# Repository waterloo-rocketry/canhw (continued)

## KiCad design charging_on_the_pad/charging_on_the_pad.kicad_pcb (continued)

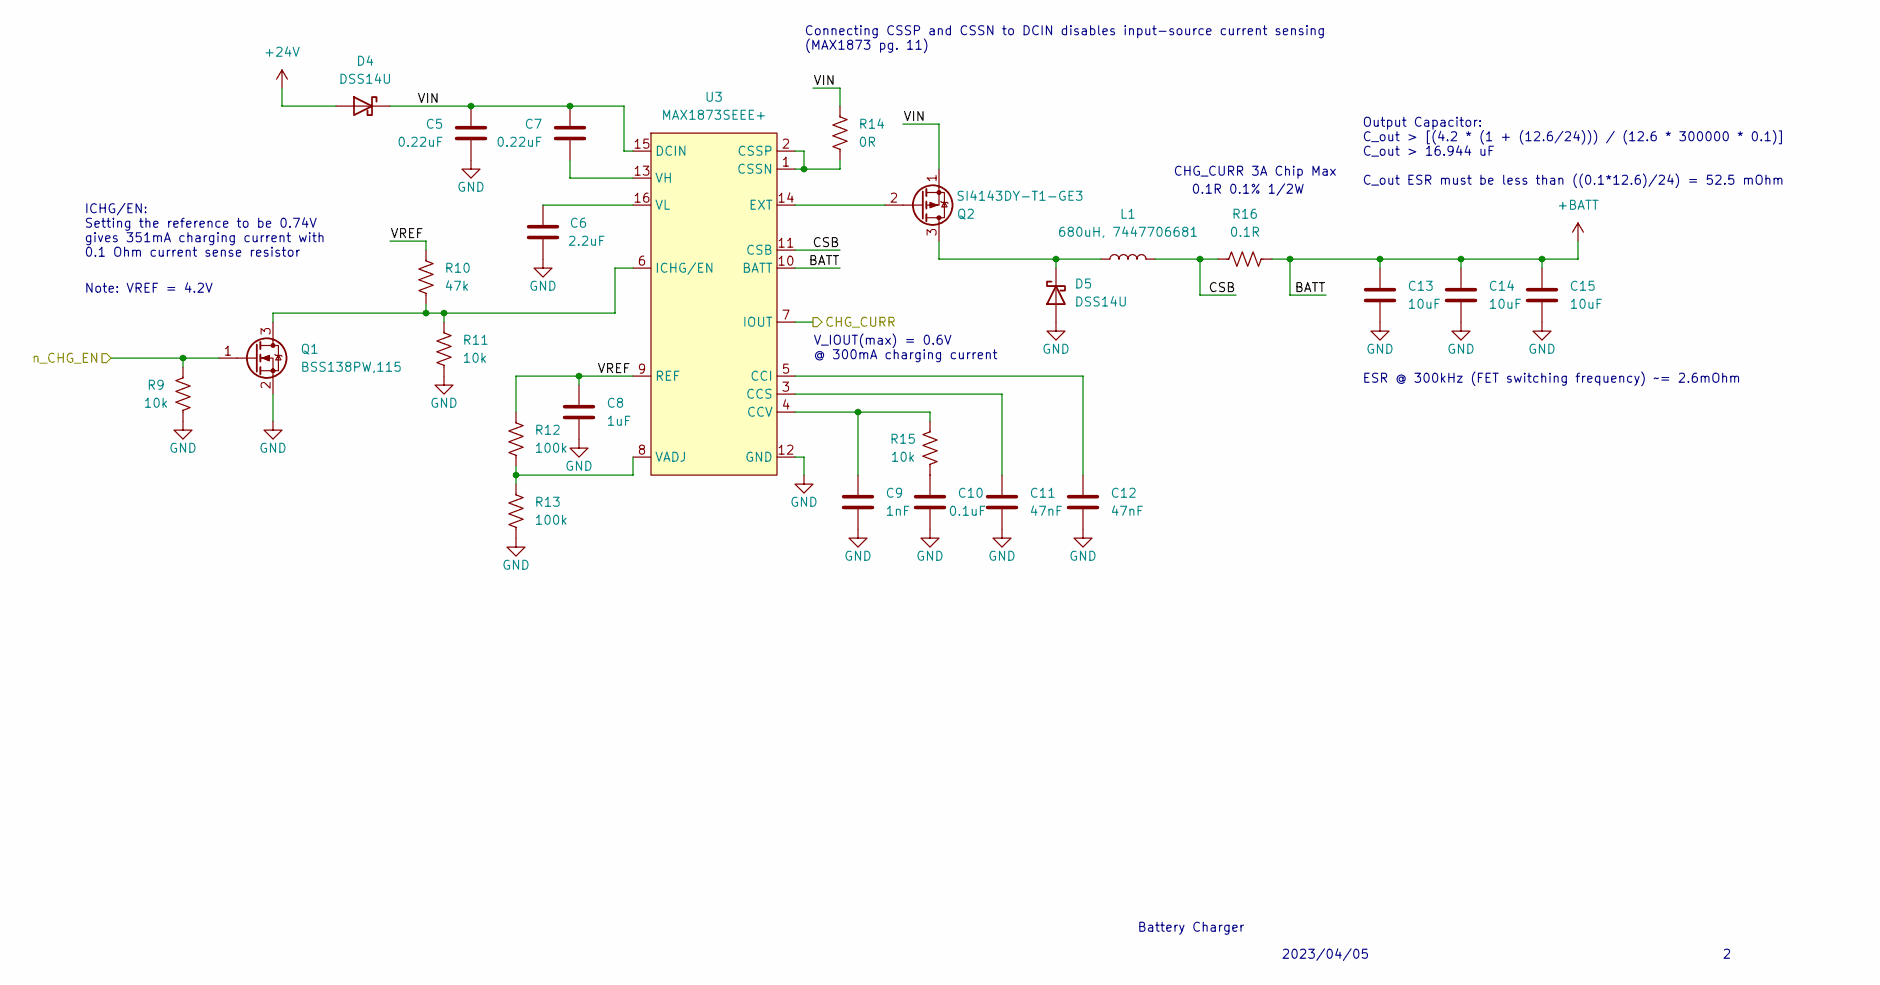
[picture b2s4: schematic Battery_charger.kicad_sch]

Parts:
C5, C7: 0.22uF; C_0805_2012Metric_Pad1.18x1.45mm_HandSolder
C6: 2.2uF; C_0805_2012Metric_Pad1.18x1.45mm_HandSolder
C8: 1uF; C_0805_2012Metric_Pad1.18x1.45mm_HandSolder
C9: 1nF; C_0805_2012Metric_Pad1.18x1.45mm_HandSolder
C10: 0.1uF; C_0805_2012Metric_Pad1.18x1.45mm_HandSolder
C11, C12: 47nF; C_0805_2012Metric_Pad1.18x1.45mm_HandSolder
C13, C14, C15: 10uF; C_0805_2012Metric_Pad1.18x1.45mm_HandSolder
D4, D5: DSS14U
L1: 680uH, 7447706681; L_12x12mm_H6mm
Q1: BSS138PW,115; SOT-323_SC-70_Handsoldering
Q2: SI4143DY-T1-GE3
R9, R11, R15: 10k; R_0805_2012Metric_Pad1.20x1.40mm_HandSolder
R10: 47k; R_0805_2012Metric_Pad1.20x1.40mm_HandSolder
R12, R13: 100k; R_0805_2012Metric_Pad1.20x1.40mm_HandSolder
R14: 0R; R_0805_2012Metric_Pad1.20x1.40mm_HandSolder
R16: 0.1R; R_1206_3216Metric_Pad1.30x1.75mm_HandSolder
U3: MAX1873SEEE+; SSOP-16_3.9x4.9mm_P0.635mm

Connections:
+24V: D4.2 (A); also elsewhere on the board
+BATT: C13.2, C14.2, C15.2, R16.1, U3.10 (BATT); also elsewhere on the board
/Battery Charger/CSB: L1.2, R16.2, U3.11 (CSB)
/Battery Charger/VIN: C5.2, C7.2, D4.1 (K), Q2.1 (S), R14.1, U3.15 (DCIN)
/Battery Charger/VREF: C8.2, R10.1, R12.1, U3.9 (REF)
/CHG_CURR: U3.7 (IOUT); also elsewhere on the board
/n_CHG_EN: Q1.1 (G), R9.2; also elsewhere on the board
GND: C5.1, C6.1, C8.1, C9.2, C10.1, C11.1, C12.1, C13.1, C14.1, C15.1, D5.2 (A), Q1.2 (S), R9.1, R11.2, R13.2, U3.12 (GND); also elsewhere on the board
unnamed: C10.2, R15.1
unnamed: D5.1 (K), L1.1, Q2.3 (D)
unnamed: Q1.3 (D), R10.2, R11.1, U3.6 (ICHG/EN)
unnamed: Q2.2 (G), U3.14 (EXT)
unnamed: C12.2, U3.5 (CCI)
unnamed: C11.2, U3.3 (CCS)
unnamed: C9.1, R15.2, U3.4 (CCV)
unnamed: R14.2, U3.1 (CSSN), U3.2 (CSSP)
unnamed: R12.2, R13.1, U3.8 (VADJ)
unnamed: C7.1, U3.13 (VH)
unnamed: C6.2, U3.16 (VL)

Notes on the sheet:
V_IOUT(max) = 0.6V @ 300mA charging current
Output Capacitor: C_out > [(4.2 * (1 + (12.6/24))) / (12.6 * 300000 * 0.1)] C_out > 16.944 uF C_out ESR must be less than ((0.1*12.6)/24) = 52.5 mOhm
CHG_CURR 3A Chip Max
Battery Charger
0.1R 0.1% 1/2W
2023/04/05
Note: VREF = 4.2V
ESR @ 300kHz (FET switching frequency) ~= 2.6mOhm
ICHG/EN: Setting the reference to be 0.74V gives 351mA charging current with 0.1 Ohm current sense resistor
Connecting CSSP and CSSN to DCIN disables input-source current sensing (MAX1873 pg. 11)

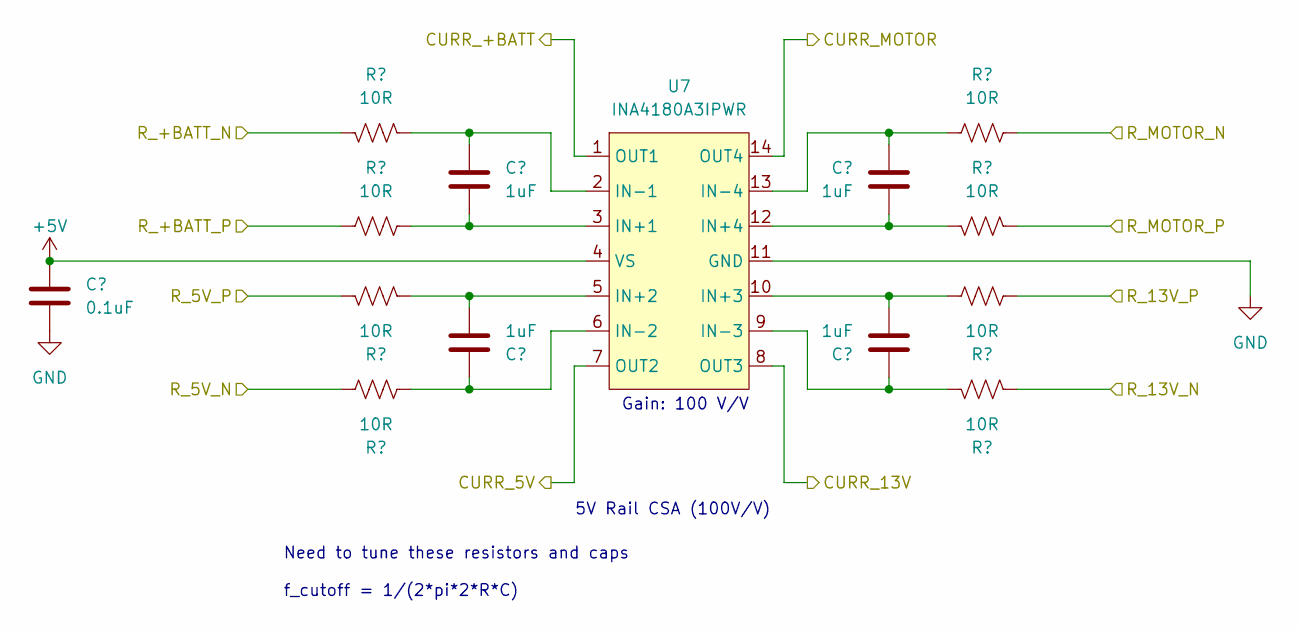
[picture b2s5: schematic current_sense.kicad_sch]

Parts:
C31: 0.1uF; C_0805_2012Metric_Pad1.18x1.45mm_HandSolder
C32, C33, C34, C35: 1uF; C_0805_2012Metric_Pad1.18x1.45mm_HandSolder
R28, R29, R30, R31, R32, R33, R34, R35: 10R; R_0805_2012Metric_Pad1.20x1.40mm_HandSolder
U7: INA4180A3IPWR; TSSOP-14_4.4x5mm_P0.65mm

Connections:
+5V: C31.1, R31.2, U7.4 (VS); also elsewhere on the board
+13V: R35.2; also elsewhere on the board
+BATT: R29.1; also elsewhere on the board
/CURR_5V: U7.7 (OUT2); also elsewhere on the board
/CURR_13V: U7.8 (OUT3); also elsewhere on the board
/CURR_+BATT: U7.1 (OUT1); also elsewhere on the board
/CURR_MOTOR: U7.14 (OUT4); also elsewhere on the board
/Power/R_5V_P: R30.1; also elsewhere on the board
/Power/R_13V_P: R34.1; also elsewhere on the board
/Power/R_+BATT_N: R28.2; also elsewhere on the board
/R_MOTOR_N: R32.2; also elsewhere on the board
/R_MOTOR_P: R33.1; also elsewhere on the board
GND: C31.2, U7.11 (GND); also elsewhere on the board
unnamed: C32.2, R29.2, U7.3 (IN+1)
unnamed: C33.2, R30.2, U7.5 (IN+2)
unnamed: C35.2, R34.2, U7.10 (IN+3)
unnamed: C34.2, R33.2, U7.12 (IN+4)
unnamed: C32.1, R28.1, U7.2 (IN-1)
unnamed: C33.1, R31.1, U7.6 (IN-2)
unnamed: C35.1, R35.1, U7.9 (IN-3)
unnamed: C34.1, R32.1, U7.13 (IN-4)

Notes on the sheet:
Gain: 100 V/V
Need to tune these resistors and caps f_cutoff = 1/(2*pi*2*R*C)
5V Rail CSA (100V/V)

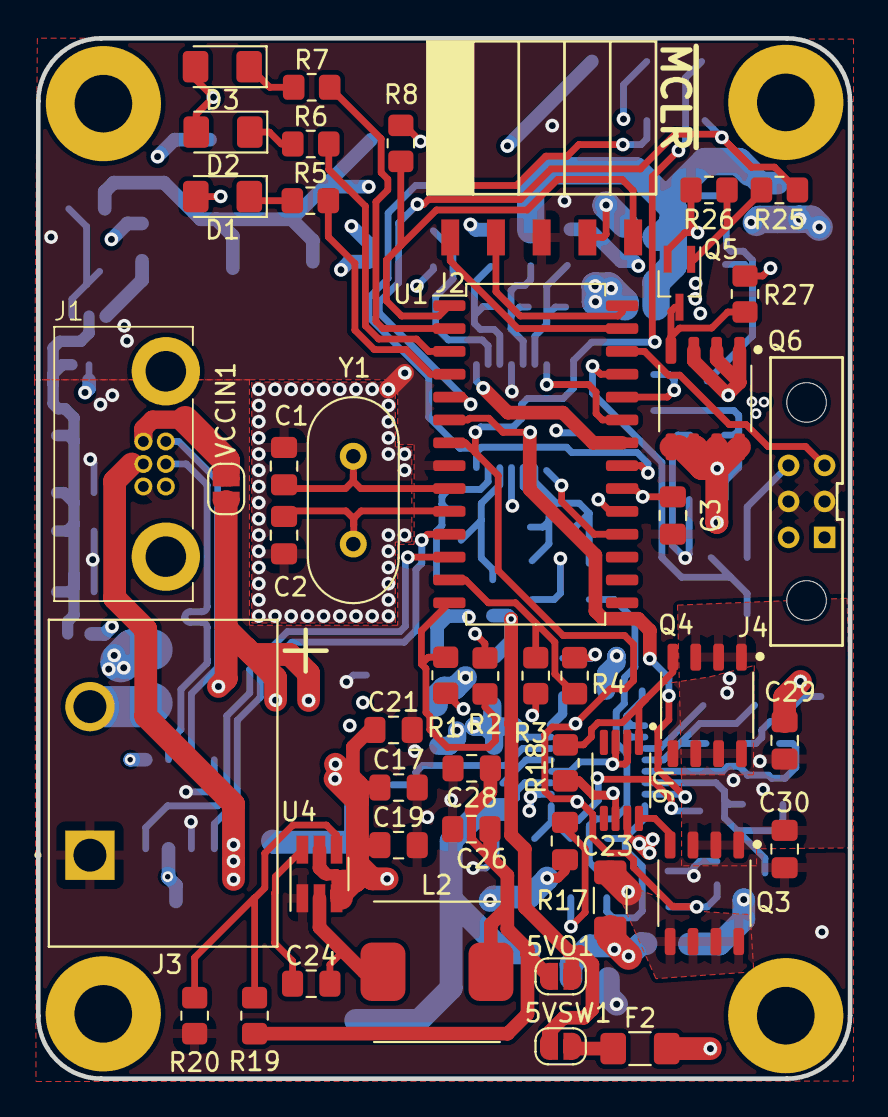
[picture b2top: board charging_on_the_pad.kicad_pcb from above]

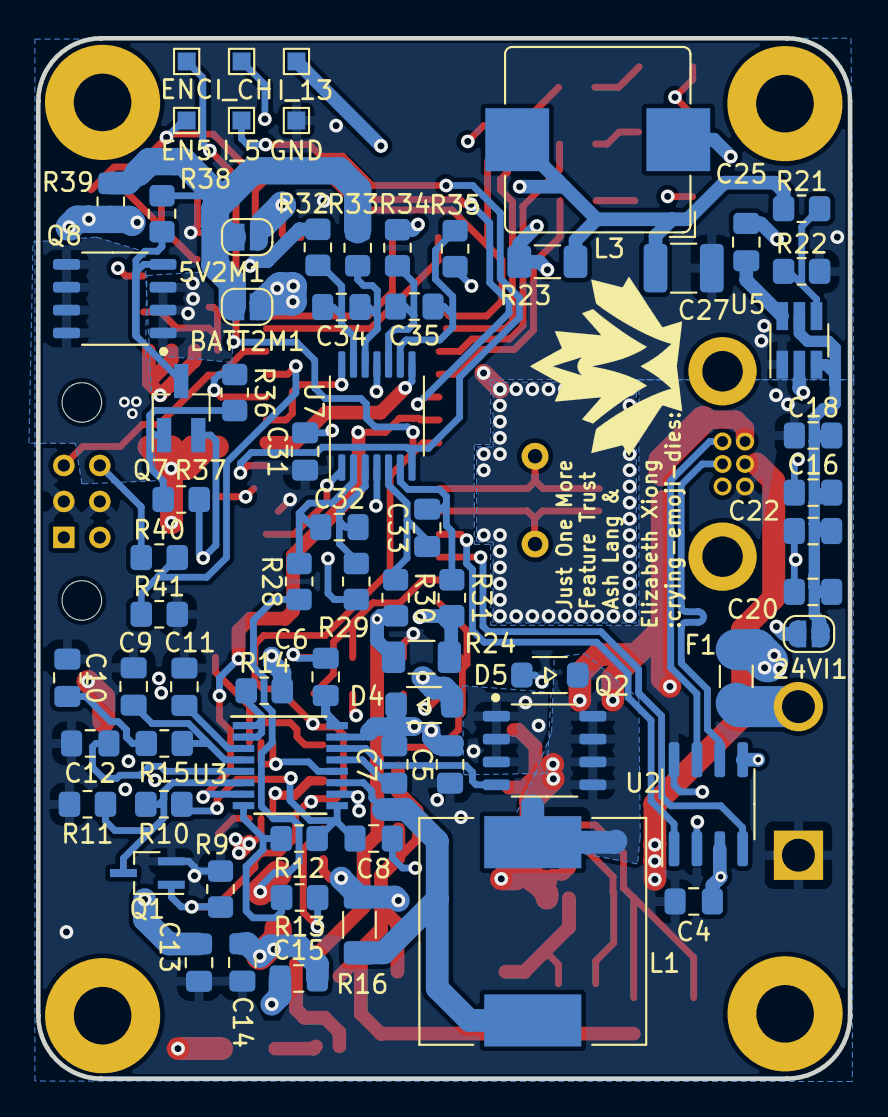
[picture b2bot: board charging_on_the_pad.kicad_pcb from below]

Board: 4 copper layers, 45.1 x 57.8 mm, 122 parts (71 on the bottom side), 80 nets.

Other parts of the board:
EN5: TestPoint; TestPoint_Pad_1.0x1.0mm
ENC: TestPoint; TestPoint_Pad_1.0x1.0mm
GND: TestPoint; TestPoint_Pad_1.0x1.0mm
I_5, I_13: TestPoint; TestPoint_Pad_1.0x1.0mm
I_CH: TestPoint; TestPoint_Pad_1.0x1.0mm
VCCIN1: SolderJumper_2_Open; SolderJumper-2_P1.3mm_Open_RoundedPad1.0x1.5mm

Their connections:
/CHG_CURR: I_CH.1; also elsewhere on the board
/CURR_5V: I_5.1; also elsewhere on the board
/CURR_13V: I_13.1; also elsewhere on the board
/EN_5V: EN5.1; also elsewhere on the board
/n_CHG_EN: ENC.1; also elsewhere on the board
GND: GND.1; also elsewhere on the board
unnamed 45: VCCIN1.1 (A); also elsewhere on the board
VCC: VCCIN1.2 (B); also elsewhere on the board

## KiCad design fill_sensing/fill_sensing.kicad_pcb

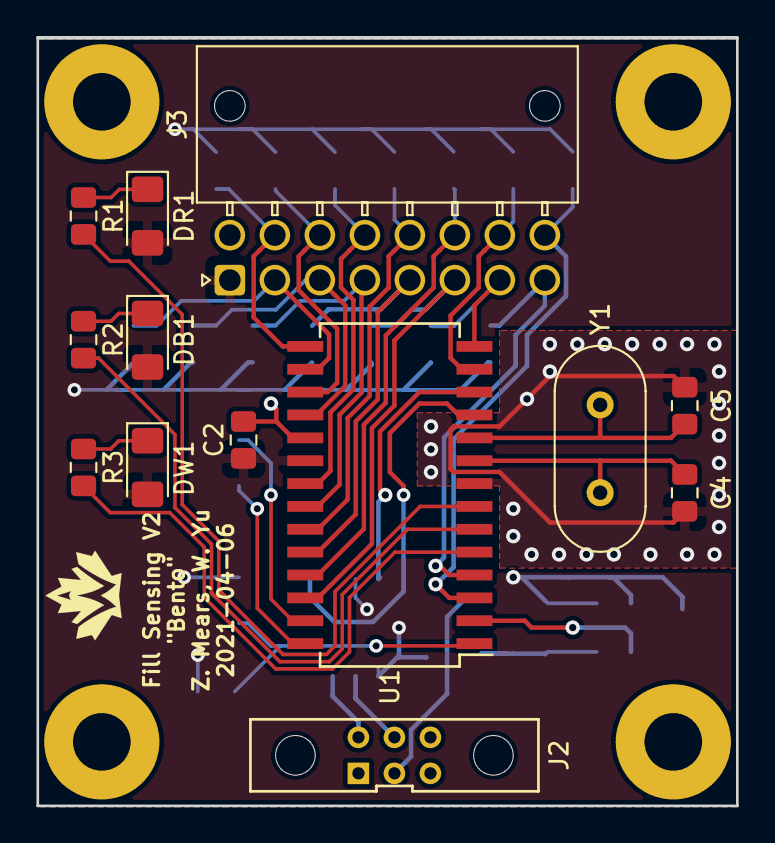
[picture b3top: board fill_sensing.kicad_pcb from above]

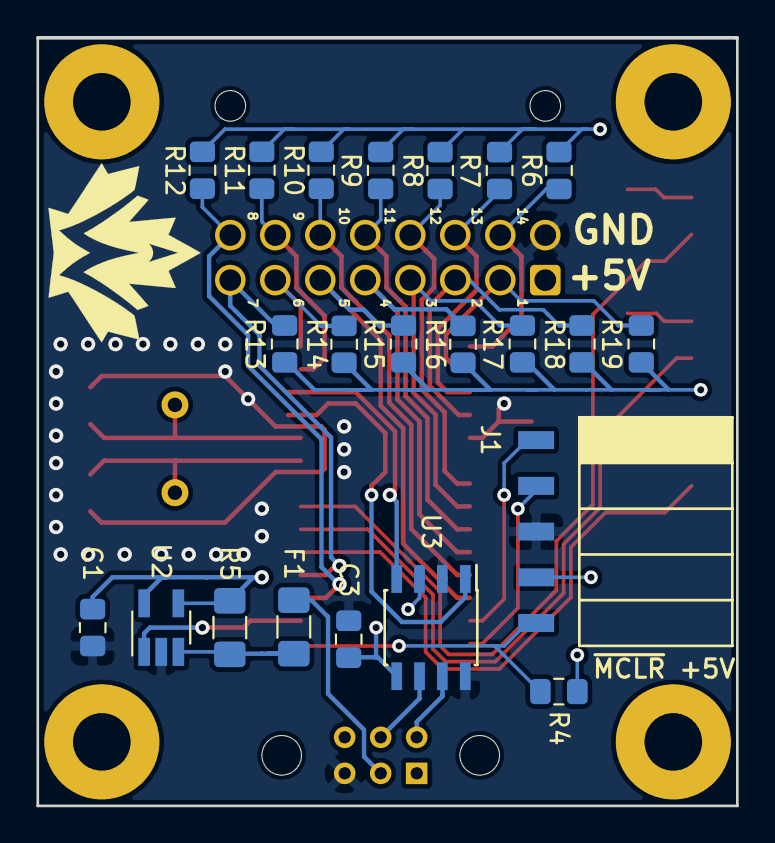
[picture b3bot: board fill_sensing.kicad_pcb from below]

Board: 2 copper layers, 38.9 x 42.7 mm, 35 parts (22 on the bottom side), 34 nets.

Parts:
C1, C2: 0.1uF; C_0805_2012Metric_Pad1.15x1.40mm_HandSolder
C3: 10uF; C_0805_2012Metric_Pad1.15x1.40mm_HandSolder
C4, C5: 27pF; C_0805_2012Metric_Pad1.15x1.40mm_HandSolder
DB1: LED; LED_1206_3216Metric_Pad1.42x1.75mm_HandSolder
DR1: LED; LED_1206_3216Metric_Pad1.42x1.75mm_HandSolder
DW1: LED; LED_1206_3216Metric_Pad1.42x1.75mm_HandSolder
F1: Polyfuse; Fuse_1206_3216Metric_Pad1.42x1.75mm_HandSolder
J1: Programming Header; PinHeader_5x2.54_SMD_90deg_952-3198-1-ND
J2: CAN Connector; connector_Harwin_M80-5000642
J3: Hall Sensor Connector; Molex_Nano-Fit_105314-xx16_2x08_P2.50mm_Horizontal
R1, R2, R3: 330R; R_0805_2012Metric_Pad1.15x1.40mm_HandSolder
R4, R6, R7, R8, R9, R10, R11, R12, R13, R14, R15, R16, R17, R18, R19: 10K; R_0805_2012Metric_Pad1.15x1.40mm_HandSolder
R5: 200mR; R_1206_3216Metric_Pad1.42x1.75mm_HandSolder
U1: PIC18F26K83; SOIC-28W_7.5x18.7mm_P1.27mm
U2: INA180; SOT-23-5_HandSoldering
U3: MCP2562; SOIC-8_3.9x4.9mm_P1.27mm
Y1: Crystal; Crystal_HC49-4H_Vertical

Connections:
+5V: C1.2, C2.1, C3.1, DB1.2, DR1.2, DW1.2, J1.4, J3.1, R4.1, R5.1, R6.1, R7.1, R8.1, R9.1, R10.1, R11.1, R12.1, R13.1, R14.1, R15.1, R16.1, R17.1, R18.1, R19.1, U1.20, U2.4, U2.5, U3.3, U3.5
/CAN_RX: U1.12, U3.4
/CAN_TX: U1.11, U3.1
/CURR_AMP: U1.2, U2.1
/HALL_1: J3.2, R19.2, U1.16
/HALL_2: J3.3, R18.2, U1.18
/HALL_3: J3.4, R17.2, U1.22
/HALL_4: J3.5, R16.2, U1.24
/HALL_5: J3.6, R15.2, U1.26
/HALL_6: J3.7, R14.2, U1.14
/HALL_7: J3.8, R13.2, U1.4
/HALL_8: J3.16, R12.2, U1.3
/HALL_9: J3.15, R11.2, U1.13
/HALL_10: J3.14, R10.2, U1.25
/HALL_11: J3.13, R9.2, U1.23
/HALL_12: J3.12, R8.2, U1.21
/HALL_13: J3.11, R7.2, U1.17
/HALL_14: J3.10, R6.2, U1.15
/ICSPCLK: J1.1, U1.27
/ICSPDAT: J1.2, U1.28
/OSC1: C4.1, U1.9, Y1.1
/OSC2: C5.1, U1.10, Y1.2
/~MCLR: J1.5, R4.2, U1.1
CANH: J2.4, U3.7
CANL: J2.5, U3.6
GND: C1.1, C2.2, C3.2, C4.2, C5.2, J1.3, J2.3, J3.9, U1.8, U1.19, U2.2, U3.2, U3.8
unnamed: DB1.1, R2.1
unnamed: DR1.1, R1.1
unnamed: DW1.1, R3.1
unnamed: F1.1, J2.2
unnamed: F1.2, R5.2, U2.3
unnamed: R1.2, U1.7
unnamed: R2.2, U1.6
unnamed: R3.2, U1.5

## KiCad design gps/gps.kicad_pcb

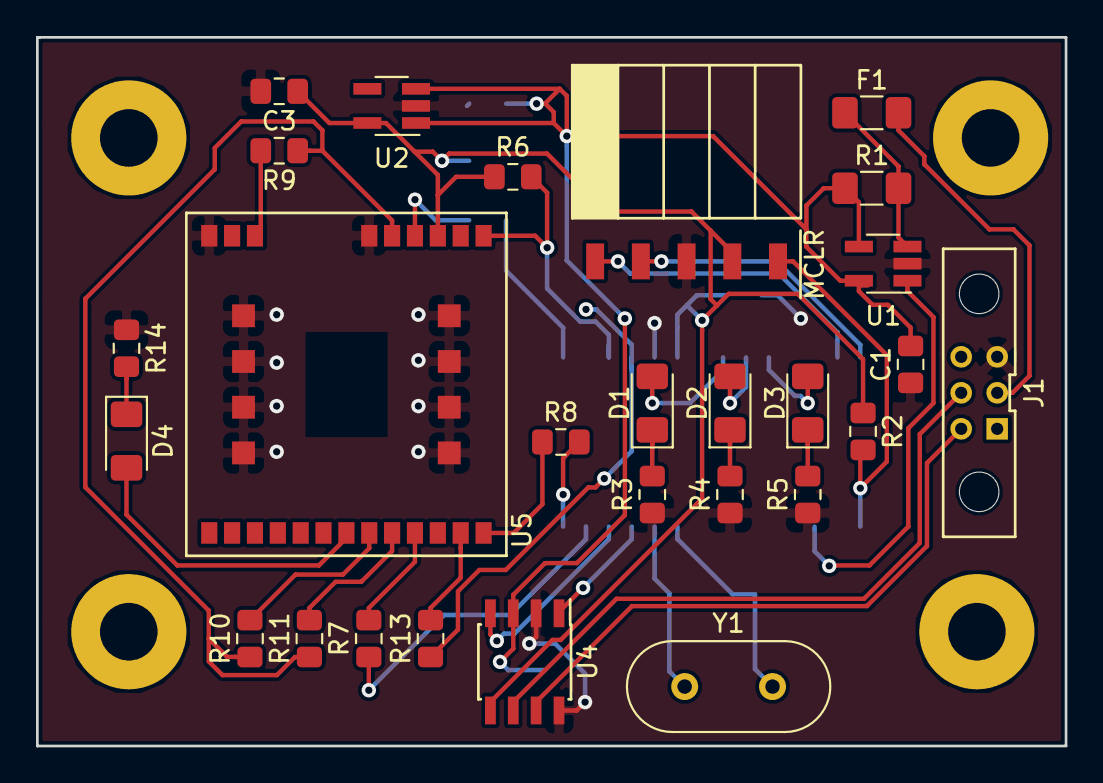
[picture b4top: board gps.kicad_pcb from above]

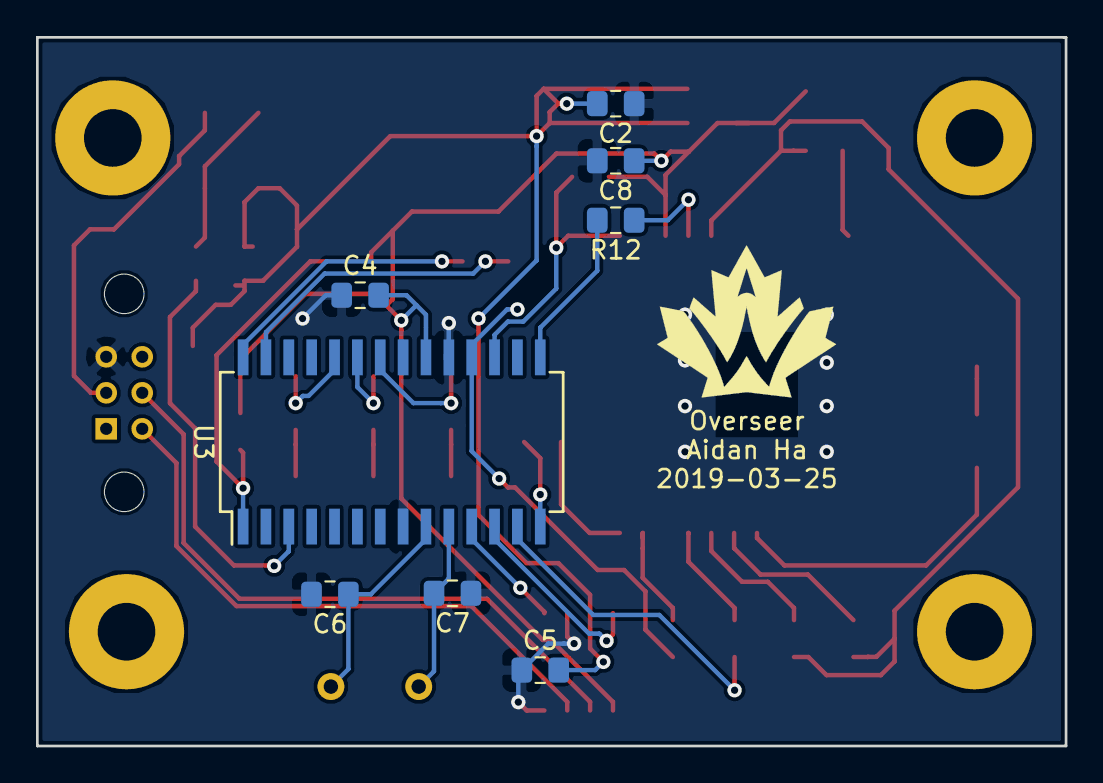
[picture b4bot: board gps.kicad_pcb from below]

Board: 2 copper layers, 57.2 x 39.4 mm, 35 parts (8 on the bottom side), 36 nets.

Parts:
C1, C4, C8: 0.1µF; C_0805_2012Metric_Pad1.15x1.40mm_HandSolder
C2, C3: 1µF; C_0805_2012Metric_Pad1.15x1.40mm_HandSolder
C5: 10uF; C_0805_2012Metric_Pad1.15x1.40mm_HandSolder
C6, C7: 26pF; C_0805_2012Metric_Pad1.15x1.40mm_HandSolder
D1, D2, D3, D4: LED; LED_1206_3216Metric_Pad1.42x1.75mm_HandSolder
F1: Polyfuse; Fuse_1206_3216Metric_Pad1.42x1.75mm_HandSolder
J1: CAN Bus Conn; connector_Harwin_M80-5000642
J2: Programming Header; PinHeader_5x2.54_SMD_90deg_952-3198-1-ND
R1: 200mR; R_1206_3216Metric_Pad1.42x1.75mm_HandSolder
R2, R6: 10k; R_0805_2012Metric_Pad1.15x1.40mm_HandSolder
R3, R4, R5, R14: 330; R_0805_2012Metric_Pad1.15x1.40mm_HandSolder
R7, R8, R12, R13: 0; R_0805_2012Metric_Pad1.15x1.40mm_HandSolder
R9: 10K; R_0805_2012Metric_Pad1.15x1.40mm_HandSolder
R10, R11: 2.2K; R_0805_2012Metric_Pad1.15x1.40mm_HandSolder
U1: INA180; SOT-23-5_HandSoldering
U2: MIC5504-3.3; SOT-23-5_HandSoldering
U3: PIC18LF26K83; SOIC-28W_7.5x18.7mm_P1.27mm
U4: MCP2562; SOIC-8_3.9x4.9mm_P1.27mm
U5: A2235-H; A2235_H
Y1: Crystal; Crystal_HC49-U_Vertical

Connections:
+3V3: C3.1, C4.2, C8.1, J2.4, R2.1, R6.1, U2.5, U3.20, U4.5, U5.3
+5V: C1.1, C2.1, C5.1, R1.1, U1.4, U1.5, U2.1, U2.3, U4.3
/CANH: J1.4, U4.7
/CANL: J1.5, U4.6
/CAN_RX: U3.12, U4.4
/CAN_TX: U3.11, U4.1
/ICSPCLK: J2.1, U3.27
/ICSPDAT: J2.2, U3.28
/ON_OFF: R7.2, U3.13
/OSC1: C6.1, U3.9, Y1.1
/OSC2: C7.1, U3.10, Y1.2
/PIC_RX_GPS_TX: R13.2, U3.18
/PIC_TX_GPS_RX: R8.2, U3.14
/POWER: U1.1, U3.3
/RESET: R6.2, U3.17, U5.1
/VOUT: R9.2, R10.2, R11.2, U5.5
/WAKEUP: R12.1, U3.15
/~MCLR: J2.5, R2.2, U3.1
GND: C1.2, C2.2, C3.2, C4.1, C5.2, C6.2, C7.2, C8.2, J1.3, J2.3, R3.2, R4.2, R5.2, R14.2, U1.2, U2.2, U3.8, U3.19, U4.2, U4.8, U5.6, U5.9, U5.23, U5.24, U5.25, U5.26, U5.27, U5.28, U5.29, U5.30
unnamed: D1.1, R3.1
unnamed: D1.2, U3.22
unnamed: D2.1, R4.1
unnamed: D2.2, U3.23
unnamed: D3.1, R5.1
unnamed: D3.2, U3.24
unnamed: D4.1, R14.1
unnamed: D4.2, U5.16
unnamed: F1.1, J1.2
unnamed: F1.2, R1.2, U1.3
unnamed: R7.1, U5.19
unnamed: R8.1, U5.22
unnamed: R9.1, U5.7
unnamed: R10.1, U5.17
unnamed: R11.1, U5.18
unnamed: R12.2, U5.4
unnamed: R13.1, U5.21

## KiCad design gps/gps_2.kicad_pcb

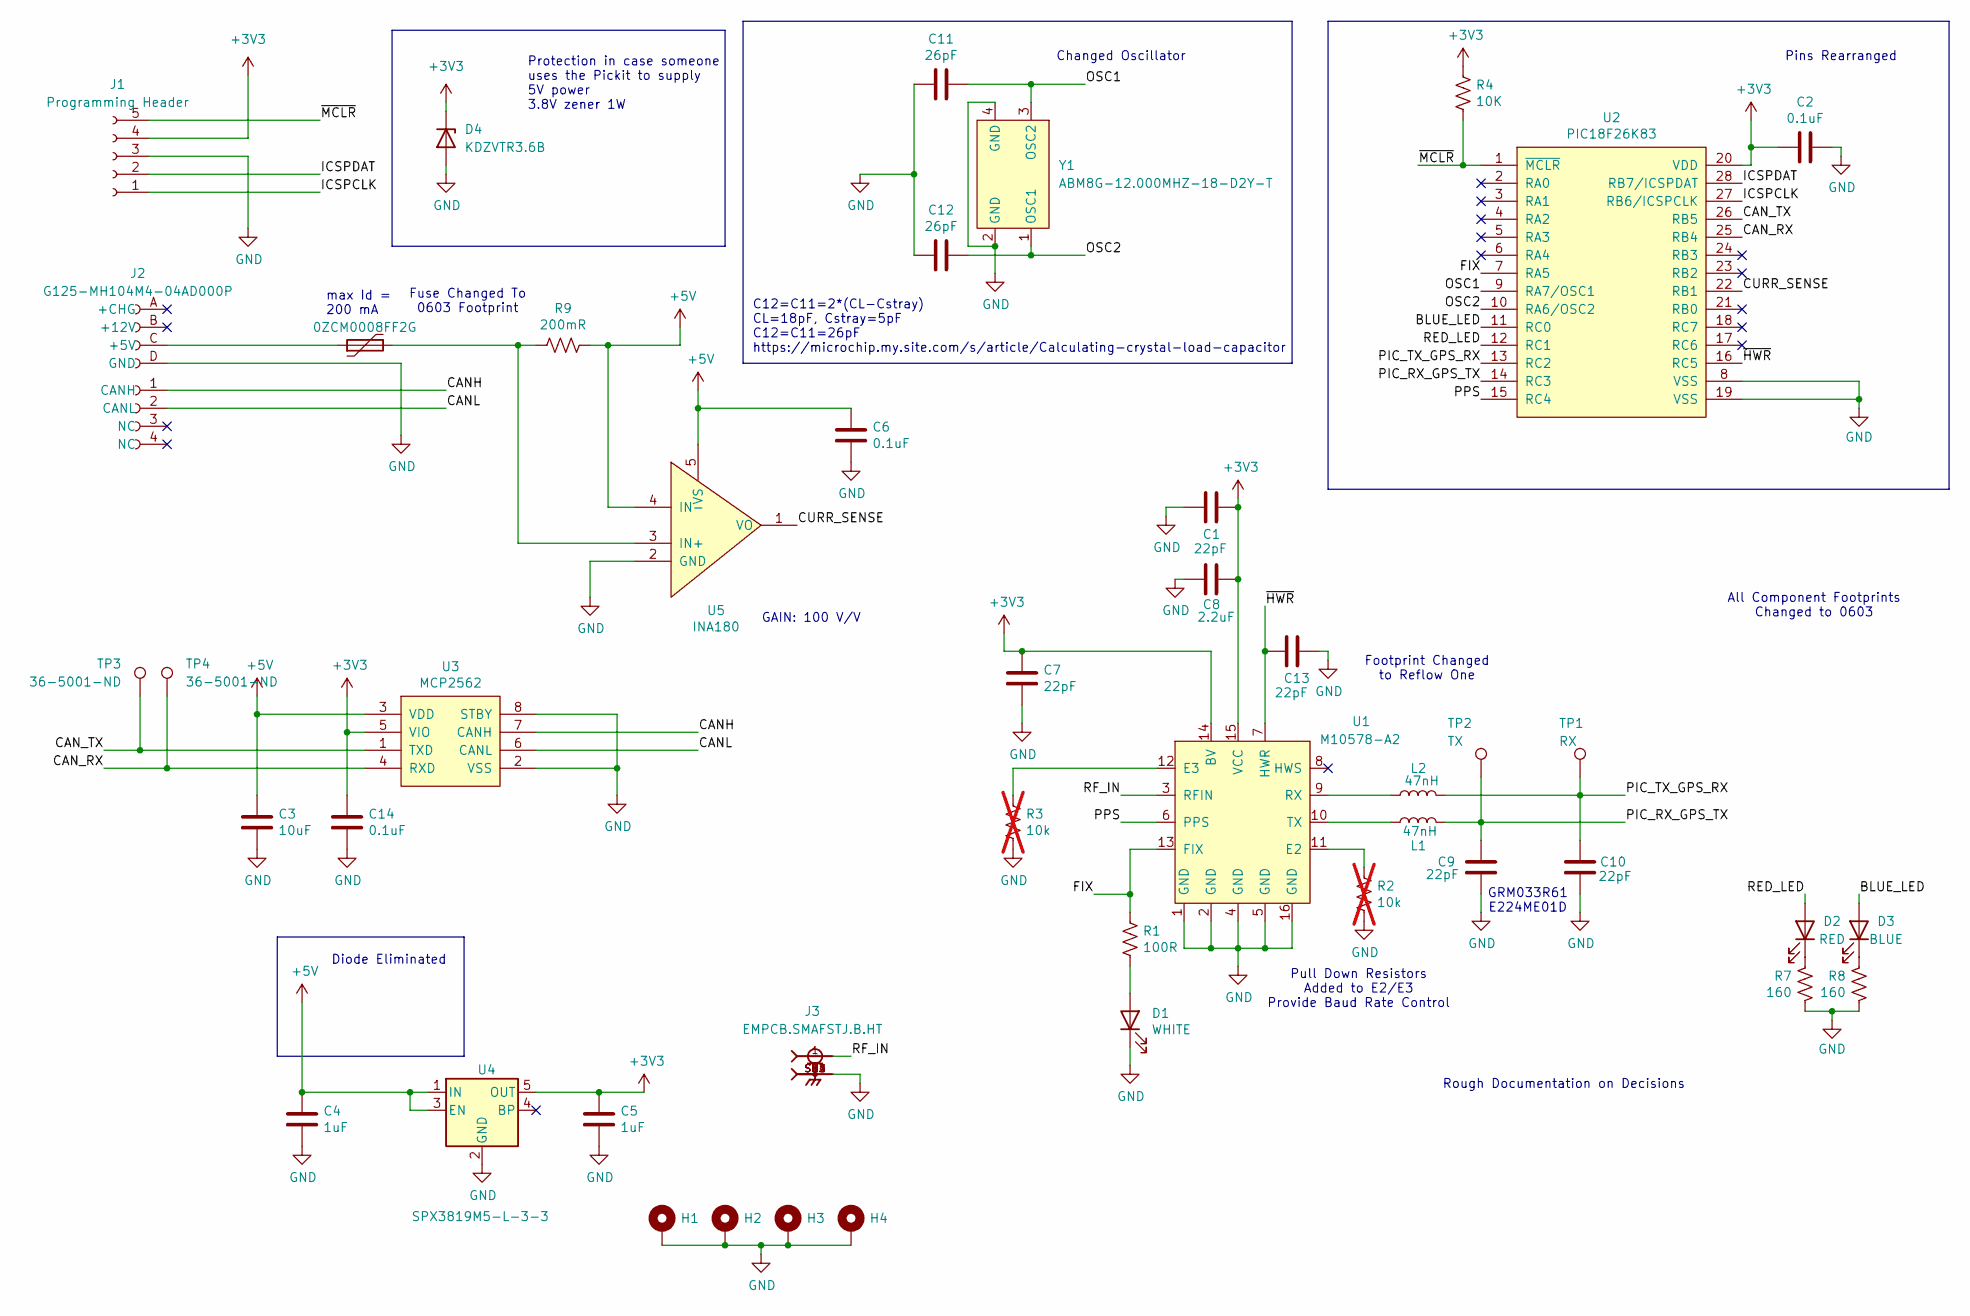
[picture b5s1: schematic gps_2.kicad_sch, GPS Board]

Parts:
C1, C7, C9, C10, C13: 22pF; C_0603_1608Metric_Pad1.08x0.95mm_HandSolder
C2, C6, C14: 0.1uF; C_0603_1608Metric_Pad1.08x0.95mm_HandSolder
C3: 10uF; C_0603_1608Metric_Pad1.08x0.95mm_HandSolder
C4, C5: 1uF; C_0603_1608Metric_Pad1.08x0.95mm_HandSolder
C8: 2.2uF; C_0603_1608Metric_Pad1.08x0.95mm_HandSolder
C11, C12: 26pF; C_0805_2012Metric_Pad1.18x1.45mm_HandSolder
D1: WHITE; LED_1206_3216Metric_Pad1.42x1.75mm_HandSolder
D2: RED; LED_1206_3216Metric_Pad1.42x1.75mm_HandSolder
D3: BLUE; LED_1206_3216Metric_Pad1.42x1.75mm_HandSolder
D4: KDZVTR3.6B; D_SOD-123F
F1: 0ZCM0008FF2G; Fuse_0603_1608Metric_Pad1.05x0.95mm_HandSolder
H1, H2, H3, H4: MountingHole; MountingHole_3.2mm_M3_Pad
J1: Programming Header; PinSocket_5x2.54_SMD_90deg_952-3198-1-ND
J2: G125-MH104M4-04AD000P; connector_Harwin_G125-MH104M4-04AD000P
J3: EMPCB.SMAFSTJ.B.HT; TAOGLAS_EMPCB.SMAFSTJ.B.HT
L1, L2: 47nH; L_0603_1608Metric_Pad1.05x0.95mm_HandSolder
R1: 100R; R_0603_1608Metric_Pad0.98x0.95mm_HandSolder
R2, R3: 10k; R_0603_1608Metric_Pad0.98x0.95mm_HandSolder; not fitted
R4: 10K; R_0603_1608Metric_Pad0.98x0.95mm_HandSolder
R7, R8: 160; R_0603_1608Metric_Pad0.98x0.95mm_HandSolder
R9: 200mR; R_0603_1608Metric_Pad0.98x0.95mm_HandSolder
TP1: RX; TestPoint_THTPad_1.0x1.0mm_Drill0.5mm
TP2: TX; TestPoint_THTPad_1.0x1.0mm_Drill0.5mm
TP3, TP4: 36-5001-ND; TestPoint_Keystone_5000-5004_Miniature
U1: M10578-A2; QFN16_M10578_ANT
U2: PIC18F26K83; SOIC-28W_7.5x18.7mm_P1.27mm
U3: MCP2562; SOIC-8_3.9x4.9mm_P1.27mm
U4: SPX3819M5-L-3-3; SOT-23-5_HandSoldering
U5: INA180; SOT-23-5_HandSoldering
Y1: ABM8G-12.000MHZ-18-D2Y-T; Crystal_SMD_Abracon_ABM8G-4Pin_3.2x2.5mm

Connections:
+3V3: C1.1, C2.2, C5.1, C7.1, C8.1, C14.1, D4.1 (K), J1.4, R4.1, U1.14 (BV), U1.15 (VCC), U2.20 (VDD), U3.5 (VIO), U4.5 (OUT)
+5V: C3.1, C4.1, C6.1, R9.1, U3.3 (VDD), U4.1 (IN), U4.3 (EN), U5.4 (IN-), U5.5 (VS)
/BLUE_LED: D3.2 (A), U2.11 (RC0)
/CANH: J2.1 (CANH), U3.7 (CANH)
/CANL: J2.2 (CANL), U3.6 (CANL)
/CAN_RX: TP4.1, U2.25 (RB4), U3.4 (RXD)
/CAN_TX: TP3.1, U2.26 (RB5), U3.1 (TXD)
/CURR_SENSE: U2.22 (RB1), U5.1 (VO)
/FIX: R1.1, U1.13 (FIX), U2.7 (RA5)
/ICSPCLK: J1.1, U2.27 (RB6/ICSPCLK)
/ICSPDAT: J1.2, U2.28 (RB7/ICSPDAT)
/OSC1: C11.1, U2.9 (RA7/OSC1), Y1.3 (OSC2)
/OSC2: C12.1, U2.10 (RA6/OSC2), Y1.1 (OSC1)
/PIC_RX_GPS_TX: C9.2, L1.2, TP2.1, U2.14 (RC3)
/PIC_TX_GPS_RX: C10.2, L2.2, TP1.1, U2.13 (RC2)
/PPS: U1.6 (PPS), U2.15 (RC4)
/RED_LED: D2.2 (A), U2.12 (RC1)
/RF_IN: J3.1, U1.3 (RFIN)
/~HWR: C13.2, U1.7 (HWR), U2.16 (RC5)
/~MCLR: J1.5, R4.2, U2.1 (~MCLR)
GND: C1.2, C2.1, C3.2, C4.2, C5.2, C6.2, C7.2, C8.2, C9.1, C10.1, C11.2, C12.2, C13.1, C14.2, D1.1 (K), D4.2 (A), H1.1, H2.1, H3.1, H4.1, J1.3, J2.D (GND), J3.SH1, J3.SH2, J3.SH3, J3.SH4, R2.2, R3.2, R7.2, R8.2, U1.1 (GND), U1.2 (GND), U1.4 (GND), U1.5 (GND), U1.16 (GND), U2.8 (VSS), U2.19 (VSS), U3.2 (VSS), U3.8 (STBY), U4.2 (GND), U5.2 (GND), Y1.2 (GND), Y1.4 (GND)
unnamed: D1.2 (A), R1.2
unnamed: D2.1 (K), R7.1
unnamed: D3.1 (K), R8.1
unnamed: F1.1, J2.C (+5V)
unnamed: R2.1, U1.11 (E2)
unnamed: R3.1, U1.12 (E3)
unnamed: L2.1, U1.9 (RX)
unnamed: L1.1, U1.10 (TX)
unnamed: F1.2, R9.2, U5.3 (IN+)

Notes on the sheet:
Pull Down Resistors Added to E2/E3 Provide Baud Rate Control
GAIN: 100 V/V
Changed Oscillator
Diode Eliminated
Rough Documentation on Decisions
Fuse Changed To 0603 Footprint
All Component Footprints Changed to 0603
Protection in case someone uses the Pickit to supply 5V power 3.8V zener 1W
Footprint Changed to Reflow One
C12=C11=2*(CL-Cstray) CL=18pF, Cstray=5pF C12=C11=26pF https://microchip.my.site.com/s/article/Calculating-crystal-load-capacitor
max Id = 200 mA
Pins Rearranged
GRM033R61 E224ME01D

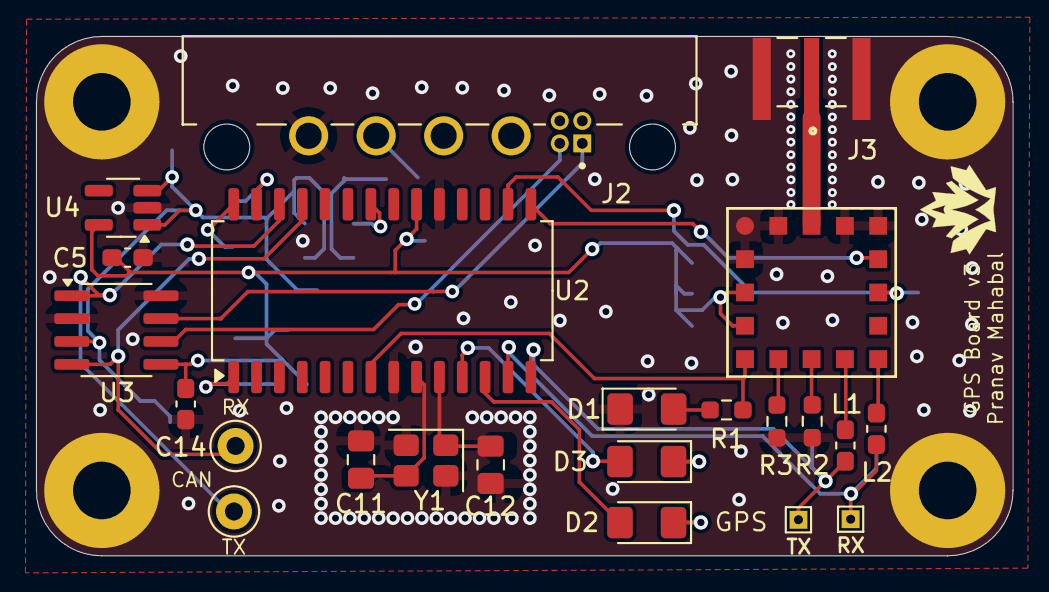
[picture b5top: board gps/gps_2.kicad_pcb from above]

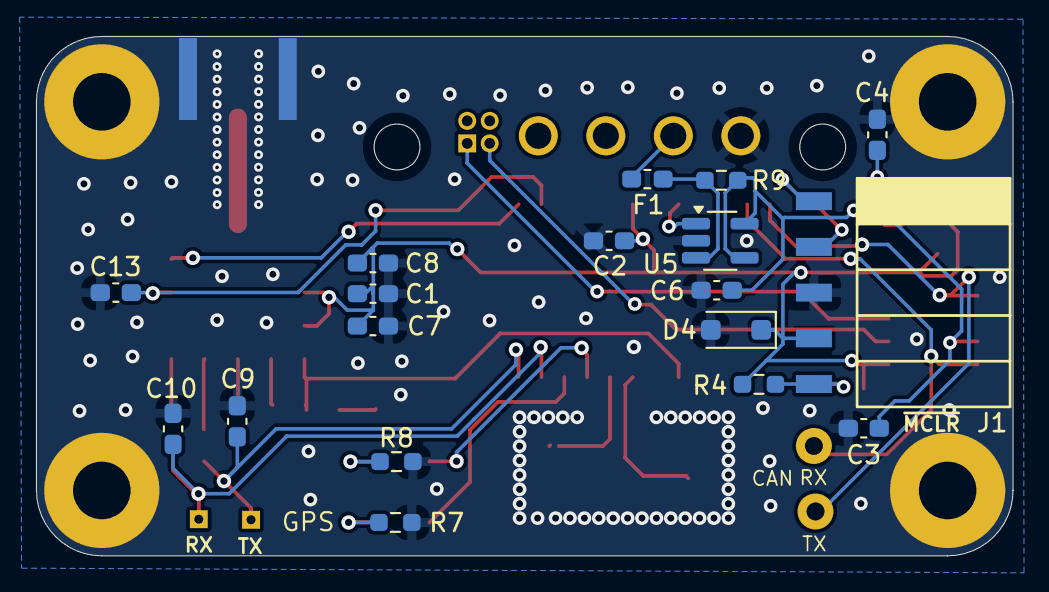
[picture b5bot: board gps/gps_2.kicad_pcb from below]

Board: 2 copper layers, 54.3 x 28.9 mm, 45 parts (18 on the bottom side), 30 nets.

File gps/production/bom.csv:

Designator,Footprint,Quantity,Value,LCSC Part #
"C1, C10, C13, C7, C9",0603,5,22pF,
"C11, C12",0805,2,26pF,
"C14, C2, C6",0603,3,0.1uF,
C3,0603,1,10uF,
"C4, C5",0603,2,1uF,
C8,0603,1,2.2uF,
D1,1206,1,WHITE,
D2,1206,1,RED,
D3,1206,1,BLUE,
D4,D_SOD-123F,1,KDZVTR3.6B,
F1,0603,1,0ZCM0008FF2G,
J1,PinSocket_5x2.54_SMD_90deg_952-3198-1-ND,1,Programming Header,
J2,connector_Harwin_G125-MH104M4-04AD000P,1,G125-MH104M4-04AD000P,
J3,TAOGLAS_EMPCB.SMAFSTJ.B.HT,1,EMPCB.SMAFSTJ.B.HT,
"L1, L2",0603,2,47nH,
R1,0603,1,100R,
"R2, R3, R4",0603,3,10k,
"R7, R8",0603,2,160,
R9,0603,1,200mR,
TP1,TestPoint_THTPad_1.0x1.0mm_Drill0.5mm,1,RX,
TP2,TestPoint_THTPad_1.0x1.0mm_Drill0.5mm,1,TX,
"TP3, TP4",TestPoint_Keystone_5000-5004_Miniature,2,36-5001-ND,
U1,QFN16_M10578_ANT,1,M10578-A2,
U2,SOIC-28W_7.5x18.7mm_P1.27mm,1,PIC18F26K83,
U3,SOIC-8_3.9x4.9mm_P1.27mm,1,MCP2562,
U4,SOT-23-5_HandSoldering,1,SPX3819M5-L-3-3,
U5,SOT-23-5_HandSoldering,1,INA180,
Y1,Crystal_SMD_Abracon_ABM8G-4Pin_3.2x2.5mm,1,ABM8G-12.000MHZ-18-D2Y-T,

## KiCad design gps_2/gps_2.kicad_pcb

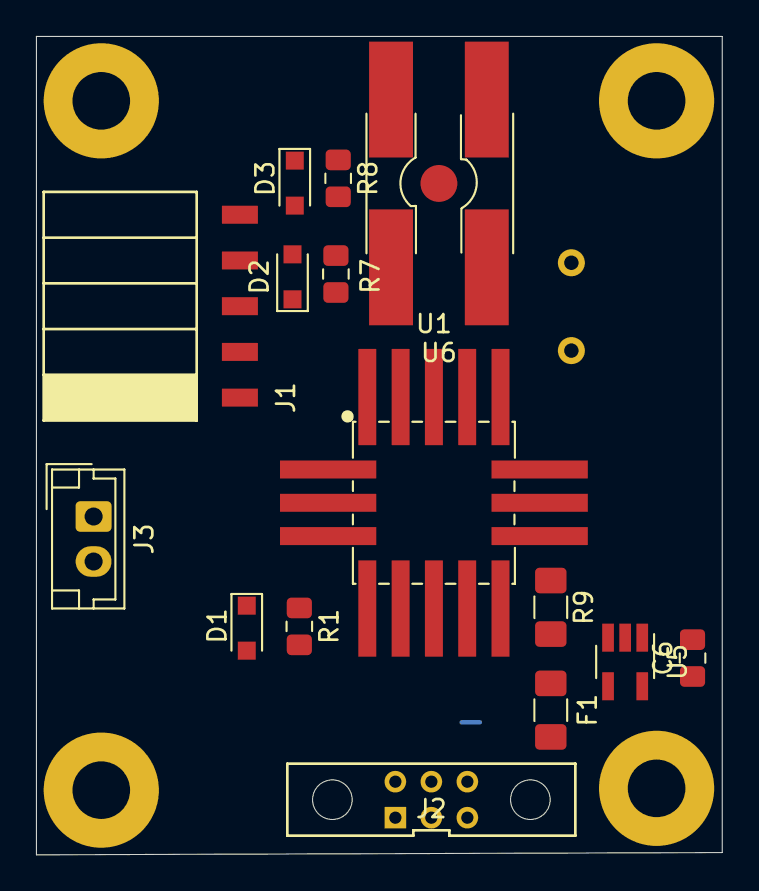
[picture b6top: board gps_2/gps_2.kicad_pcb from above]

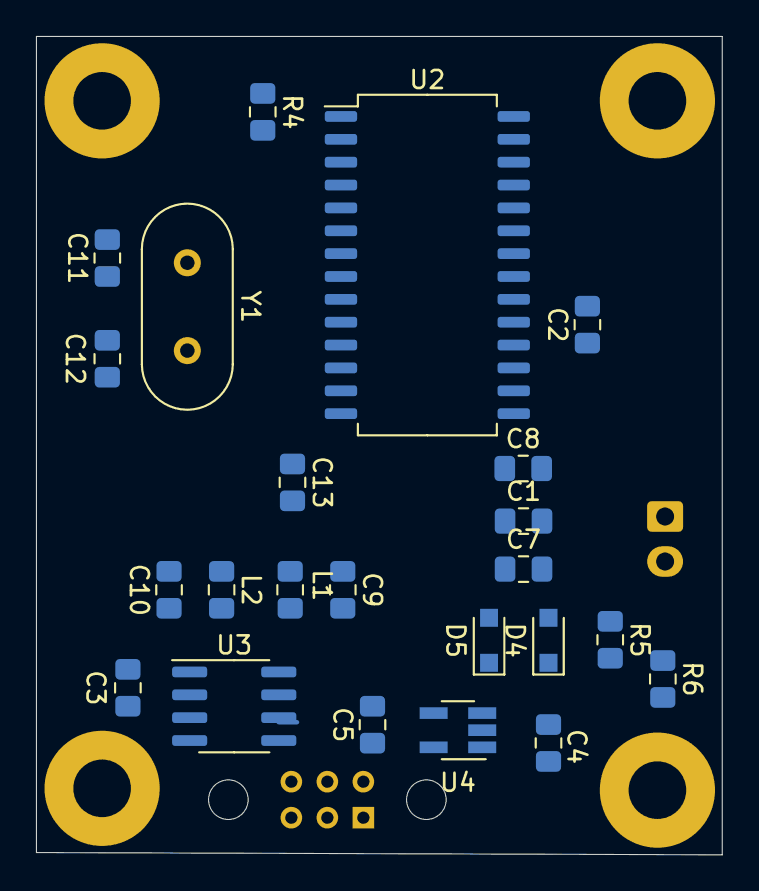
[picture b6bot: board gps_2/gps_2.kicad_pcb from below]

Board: 2 copper layers, 38.1 x 45.5 mm, 38 parts (23 on the bottom side), 31 nets.

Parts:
C1, C7, C9, C10, C13: 22pF; C_0805_2012Metric_Pad1.15x1.40mm_HandSolder
C2, C6: 0.1uF; C_0805_2012Metric_Pad1.15x1.40mm_HandSolder
C3: 10uF; C_0805_2012Metric_Pad1.15x1.40mm_HandSolder
C4, C5: 1uF; C_0805_2012Metric_Pad1.15x1.40mm_HandSolder
C8: 2.2uF; C_0805_2012Metric_Pad1.15x1.40mm_HandSolder
C11, C12: 26pF; C_0805_2012Metric_Pad1.15x1.40mm_HandSolder
D1: WHITE; D_SOD-323_HandSoldering
D2: RED; D_SOD-323_HandSoldering
D3: BLUE; D_SOD-323_HandSoldering
D4, D5: CUS08F30; D_SOD-323_HandSoldering
F1: Polyfuse; Fuse_1206_3216Metric_Pad1.42x1.75mm_HandSolder
J1: Programming Header; PinHeader_5x2.54_SMD_90deg_952-3198-1-ND
J2: CAN Bus Conn; connector_Harwin_M80-5000642
J3: Aux. bat. conn.; JST_EH_B2B-EH-A_1x02_P2.50mm_Vertical
L1, L2: 47nH; L_0805_2012Metric_Pad1.15x1.40mm_HandSolder
R1: 100R; R_0805_2012Metric_Pad1.15x1.40mm_HandSolder
R4, R6: 10K; R_0805_2012Metric_Pad1.15x1.40mm_HandSolder
R5: 15K; R_0805_2012Metric_Pad1.15x1.40mm_HandSolder
R7, R8: 160; R_0805_2012Metric_Pad1.15x1.40mm_HandSolder
R9: 200mR; R_1206_3216Metric_Pad1.42x1.75mm_HandSolder
U1: M10578-A2
U2: PIC18F26K83; SOIC-28W_7.5x18.7mm_P1.27mm
U3: MCP2562; SOIC-8_3.9x4.9mm_P1.27mm
U4: MIC5504-3.3; SOT-23-5_HandSoldering
U5: INA180; SOT-23-5_HandSoldering
U6: SMA_CONN; CONSMA001-SMD-G
Y1: Crystal; Crystal_HC49-4H_Vertical

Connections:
+3V3: C1.1, C2.2, C5.1, C7.1, C8.1, J1.4, R4.1, U1.14, U1.15, U2.20, U3.5, U4.5
+5V: C3.1, C6.1, D5.2, R9.1, U3.3, U5.4, U5.5
/AUX_BAT_V: R5.2, R6.1, U2.4
/CANH: J2.4, U3.7
/CANL: J2.5, U3.6
/CAN_RX: U2.12, U3.4
/CAN_TX: U2.11, U3.1
/CURR_SENSE: U2.3, U5.1
/FIX: R1.1, U1.13, U2.14
/ICSPCLK: J1.1, U2.27
/ICSPDAT: J1.2, U2.28
/OSC1: C11.1, U2.9, Y1.1
/OSC2: C12.1, U2.10, Y1.2
/PIC_RX_GPS_TX: C9.2, L1.2, U2.18
/PIC_TX_GPS_RX: C10.2, L2.2, U2.17
/PPS: U1.6, U2.15
/RF_IN: U1.3, U6.5
/~HWR: C13.2, U1.7, U2.13
/~MCLR: J1.5, R4.2, U2.1
GND: C1.2, C2.1, C3.2, C4.2, C5.2, C6.2, C7.2, C8.2, C9.1, C10.1, C11.2, C12.2, C13.1, D1.1, J1.3, J2.3, J3.1, R6.2, R7.2, R8.2, U1.1, U1.2, U1.4, U1.5, U1.16, U2.8, U2.19, U3.2, U3.8, U4.2, U5.2, U6.1, U6.2, U6.3, U6.4
unnamed: C4.1, D4.1, D5.1, U4.1, U4.3
unnamed: D1.2, R1.2
unnamed: D2.1, R7.1
unnamed: D2.2, U2.22
unnamed: D3.1, R8.1
unnamed: D3.2, U2.23
unnamed: D4.2, J3.2, R5.1
unnamed: F1.1, J2.2
unnamed: F1.2, R9.2, U5.3
unnamed: L1.1, U1.10
unnamed: L2.1, U1.9
